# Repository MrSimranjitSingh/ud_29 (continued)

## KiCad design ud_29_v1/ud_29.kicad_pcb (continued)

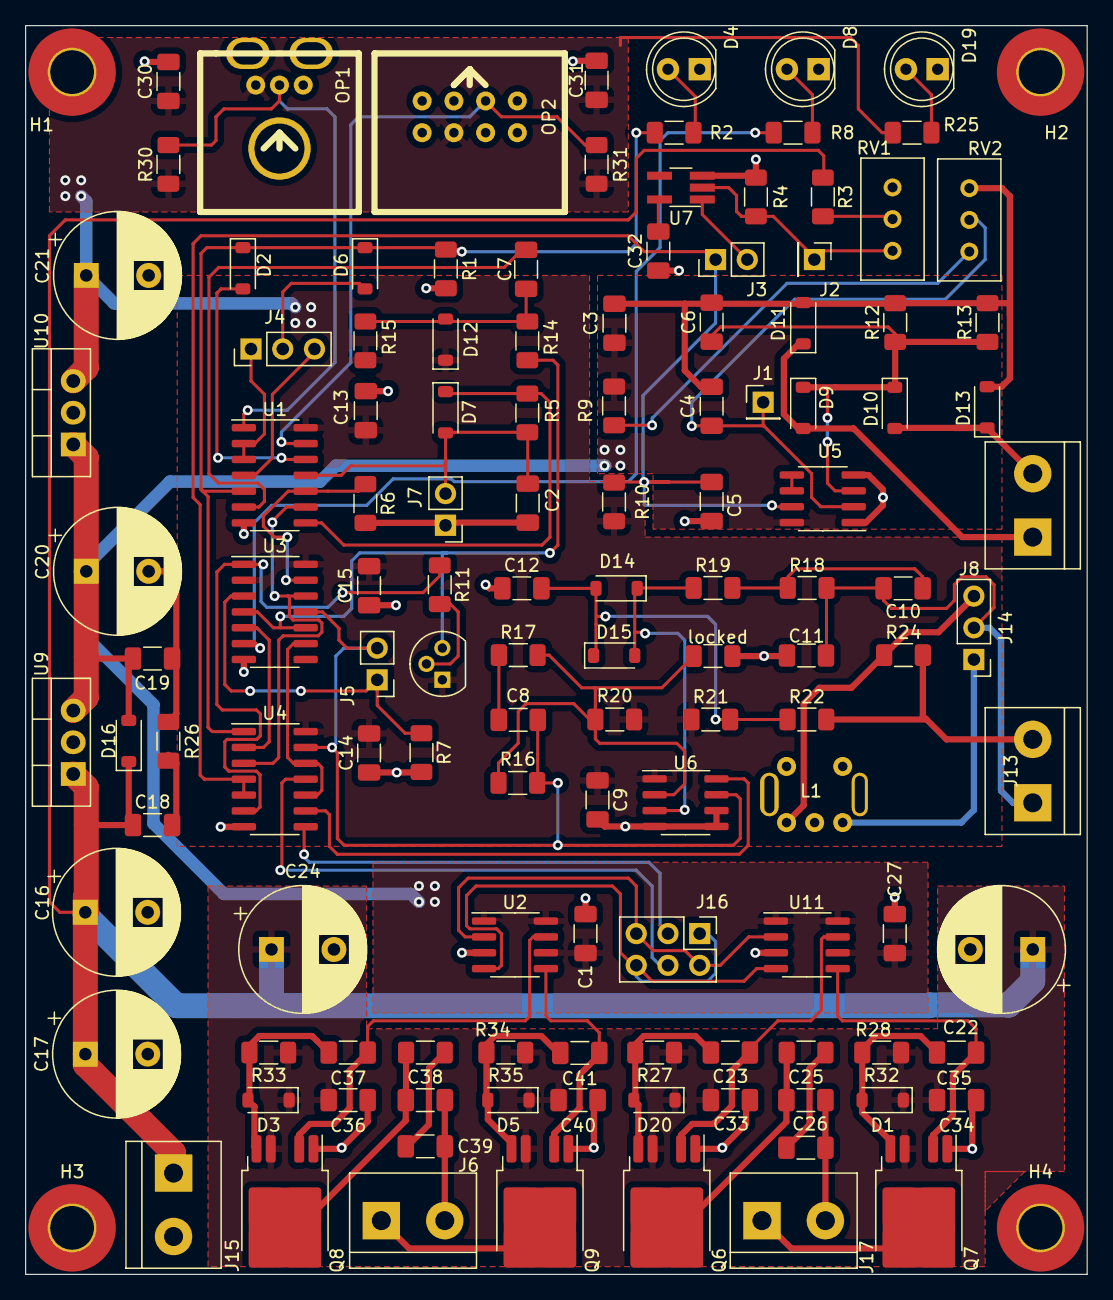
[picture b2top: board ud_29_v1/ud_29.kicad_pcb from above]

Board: 2 copper layers, 85.0 x 100.0 mm, 128 parts (0 on the bottom side), 69 nets.

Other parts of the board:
locked: 470R; R_1206_3216Metric_Pad1.30x1.75mm_HandSolder

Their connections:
GND: locked.2; also elsewhere on the board
unnamed 61: locked.1; also elsewhere on the board
